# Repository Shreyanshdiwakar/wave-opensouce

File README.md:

# Wave - Open Source Analog Keyboard

I use the two prototypes shown above as my daily drivers for both coding and gaming. They work well, and the current state of the web configurator is sufficient for seamlessly switching between coding and gaming modes. The current layout of my prototypes is Mac ISO azerty (FR).

## Videos

### 3D Printing Process

▶️ [Watch 3D Printing Process Video](assets/3dprinter.mp4)

### Keyboard Demonstration
▶️ [Watch Keyboard Demonstration Video](assets/keyboard.mp4)

Other videos:
- ▶️ [PCB overview](assets/pcb.mp4)
- ▶️ [Rev 2 demonstration](assets/rev%202.mp4)

## Features

- **Analog Input:** Each key detects varying levels of pressure thanks to Hall Effect technology, allowing for a more responsive and sensitive typing experience.
- **Rapid Trigger Support:** Enables keys to actuate without fully releasing, allowing for faster response times during intense usage (e.g., gaming or rapid typing).
- **Continuous Rapid Trigger:** For keys that require repeated pressing (e.g., in gaming), this feature allows automatic repeated key input with a single press.
- **Tap and Hold Functionality:** Each key can be assigned two functions. A tap function for quick presses and a hold function for longer presses. This is ideal for combining shortcuts or creating multi-functional keys, such as assigning the right Shift key to act as an arrow up when tapped.
- **Web-Based Configurator:** Allows customization of key sensitivity and rapid trigger settings, with future updates planned to enable key mapping and expanded functionality. (see [screenshot](assets/web-configurator-screenshot.png))

## Todos

This is still a work in progress, the first revision is working flawlessly but it is not that configurable yet. Here is some of the things I'm working on right now

- [x] PCB Rev 2.0
- [ ] Explore other MCUs
  - [ ] esp32-s3 (in progress)
  - [ ] nRF52840
  - [ ] RP2354 ?
- [ ] Add Bluetooth
- [ ] Configure layout and key mapping from the web interface
- [ ] Improve performances

## Links

- [keyboard layout](http://www.keyboard-layout-editor.com/#/gists/9dc992fd631d9f29cc5bdf738b10b4e4)

## Misc

### References

- ~~[RP2040 Datasheet](https://datasheets.raspberrypi.com/rp2040/rp2040-datasheet.pdf)~~
- ~~[RP2040 Hardware Design](https://datasheets.raspberrypi.com/rp2040/hardware-design-with-rp2040.pdf)~~
- ~~[kb2040 doc](https://learn.adafruit.com/adafruit-kb2040/downloads)~~
- ~~[RPi Pico Debugger Shoe](https://github.com/ShawnHymel/rpi-pico-debugger-shoe)~~
- [Dilemma keyboard](https://github.com/Bastardkb/Dilemma)
- [0xB2 - splinky](https://github.com/plut0nium/0xB2)
- [Sub Reddit](https://www.reddit.com/r/PrintedCircuitBoard/search/?q=rp2040&restrict_sr=1&sr_nsfw=&include_over_18=1)
- [layout/design ref](https://geekhack.org/index.php?topic=103671.0)
- [cirque trackpad](https://www.cirque.com/glidepoint-circle-trackpads)
- [MagLev_Switch_MX](https://github.com/famichu/MagLev_Switch_MX)
- [Anatomy of a keyboard](https://matt3o.com/anatomy-of-a-keyboard/)
- [Switches/Stabs Kicad footprints from ebastler/marbastlib](https://github.com/ebastler/marbastlib)
- [Reddit Post about someone building a lekker switch based keyboard](https://www.reddit.com/r/PrintedCircuitBoard/comments/152kt63/review_request_analog_hall_effect_75_iso_keyboard/)
- [Riskable projects](https://github.com/riskable)
- [Fluxpad with lekker switches](https://github.com/sssata/fluxpad)
- [STM32F411CEU6 documentation](https://www.st.com/en/microcontrollers-microprocessors/stm32f411ce.html#documentation)
- [Wooting 60HE pcb](https://github.com/heiso/macrolev/tree/main/ref/Wooting-60HE)
- [Connecting to uncommon HID devices](https://developer.chrome.com/articles/hid)
- [HID Descriptor parser](https://eleccelerator.com/usbdescreqparser/)
- [peppapighs HE8 keyboard](https://github.com/peppapighs/HE8)
- [peppapighs libhmk library](https://github.com/peppapighs/libhmk)
- [nuphy configurator demo](https://drive.nuphy.io/?isDemoMode=true)
- [geonworks configurator demo](https://venom.how/)
- [wooting configurator demo](https://wootility.io/)

### Tooling

- [QMK keyboard test](https://config.qmk.fm/#/test)
- [Keyboard ghosting interactive demonstration](https://www.microsoft.com/applied-sciences/projects/anti-ghosting-demo)
- [Kicad lib marbastlib](https://github.com/ebastler/marbastlib)
- [Debug HardFault](https://interrupt.memfault.com/blog/cortex-m-hardfault-debug)
- [ai03 Plate Generator](https://kbplate.ai03.com/)
- [JLC2KiCad_lib](https://github.com/TousstNicolas/JLC2KiCad_lib)

Add footprints and symbols from jlcpcb with this cmd

```bash
JLC2KiCadLib <...LCSC refs> -dir JLCPCB -symbol_lib JLCPCB
```

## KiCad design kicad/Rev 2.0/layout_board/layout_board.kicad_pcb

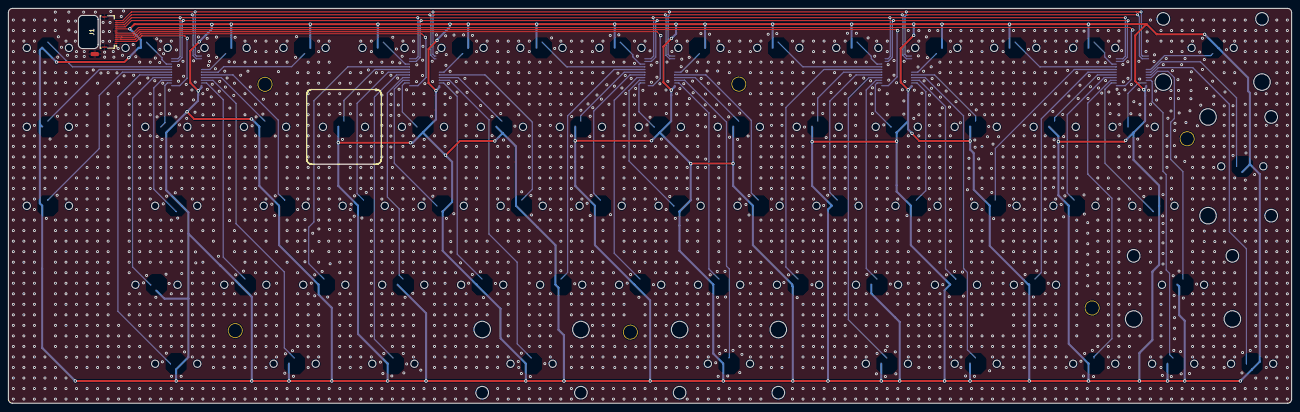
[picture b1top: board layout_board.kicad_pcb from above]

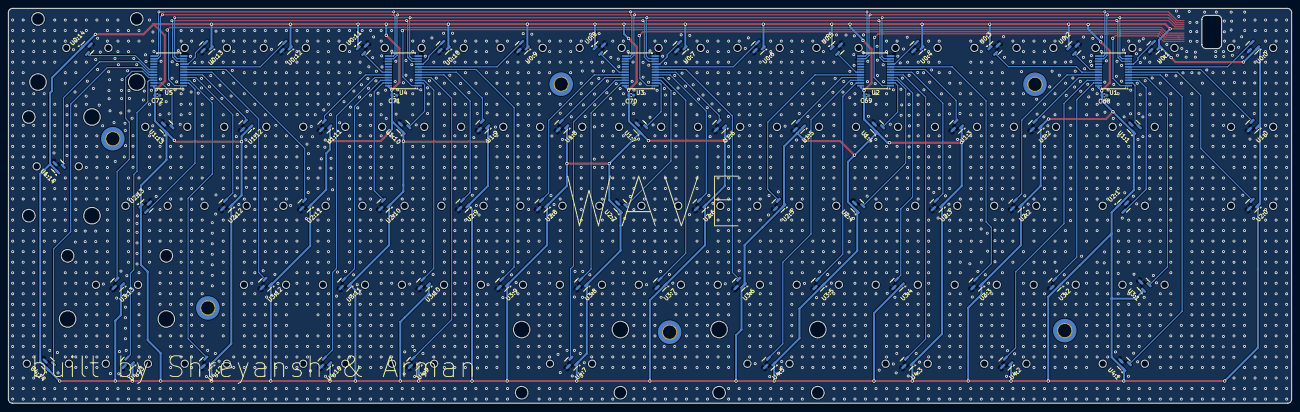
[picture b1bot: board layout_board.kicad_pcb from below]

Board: 2 copper layers, 309.6 x 95.2 mm, 78 parts (77 on the bottom side), 78 nets.

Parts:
C68, C69, C70, C71, C72: 100n; C_0402_1005Metric_Pad0.74x0.62mm_HandSolder
J1: HC-FPC-05-10-12RLTAG; FPC-SMD_12P-P0.50_HCTL_HC-FPC-05-10-12RLTAG
U0:0, U0:1, U0:2, U0:3, U0:4, U0:5, U0:6, U0:7, U0:8, U0:9, U0:10, U0:11, U0:12, U0:13, U0:14, U1:0, U1:1, U1:2, U1:3, U1:4, U1:5, U1:6, U1:7, U1:8, U1:9, U1:10, U1:11, U1:12, U1:13, U1:14, U2:0, U2:1, U2:2, U2:3, U2:4, U2:5, U2:6, U2:7, U2:8, U2:9, U2:10, U2:11, U2:12, U2:13, U3:1, U3:2, U3:3, U3:4, U3:5, U3:6, U3:7, U3:8, U3:9, U3:10, U3:11, U3:12, U3:13, U4:1, U4:2, U4:3, U4:5, U4:7, U4:9, U4:10, U4:12, U4:13, U4:14: GH39FKSW; SOT-23
U1, U2, U3, U4, U5: CD4067BPWR; SSOP-24_5.3x8.2mm_P0.65mm

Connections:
+3.3VA: C68.1, C69.1, C70.1, C71.1, C72.1, J1.8, U0:0.1 (VDD), U0:1.1 (VDD), U0:2.1 (VDD), U0:3.1 (VDD), U0:4.1 (VDD), U0:5.1 (VDD), U0:6.1 (VDD), U0:7.1 (VDD), U0:8.1 (VDD), U0:9.1 (VDD), U0:10.1 (VDD), U0:11.1 (VDD), U0:12.1 (VDD), U0:13.1 (VDD), U0:14.1 (VDD), U1.24 (VDD), U1:0.1 (VDD), U1:1.1 (VDD), U1:2.1 (VDD), U1:3.1 (VDD), U1:4.1 (VDD), U1:5.1 (VDD), U1:6.1 (VDD), U1:7.1 (VDD), U1:8.1 (VDD), U1:9.1 (VDD), U1:10.1 (VDD), U1:11.1 (VDD), U1:12.1 (VDD), U1:13.1 (VDD), U1:14.1 (VDD), U2.24 (VDD), U2:0.1 (VDD), U2:1.1 (VDD), U2:2.1 (VDD), U2:3.1 (VDD), U2:4.1 (VDD), U2:5.1 (VDD), U2:6.1 (VDD), U2:7.1 (VDD), U2:8.1 (VDD), U2:9.1 (VDD), U2:10.1 (VDD), U2:11.1 (VDD), U2:12.1 (VDD), U2:13.1 (VDD), U3.24 (VDD), U3:1.1 (VDD), U3:2.1 (VDD), U3:3.1 (VDD), U3:4.1 (VDD), U3:5.1 (VDD), U3:6.1 (VDD), U3:7.1 (VDD), U3:8.1 (VDD), U3:9.1 (VDD), U3:10.1 (VDD), U3:11.1 (VDD), U3:12.1 (VDD), U3:13.1 (VDD), U4.24 (VDD), U4:1.1 (VDD), U4:2.1 (VDD), U4:3.1 (VDD), U4:5.1 (VDD), U4:7.1 (VDD), U4:9.1 (VDD), U4:10.1 (VDD), U4:12.1 (VDD), U4:13.1 (VDD), U4:14.1 (VDD), U5.24 (VDD)
/ADC0: J1.2, U1.1 (COMMONOUT/IN)
/ADC1: J1.3, U2.1 (COMMONOUT/IN)
/ADC2: J1.4, U3.1 (COMMONOUT/IN)
/ADC3: J1.5, U4.1 (COMMONOUT/IN)
/ADC4: J1.6, U5.1 (COMMONOUT/IN)
/AMUX0:0: U0:1.2 (VOUT), U1.9 (0)
/AMUX0:1: U0:0.2 (VOUT), U1.8 (1)
/AMUX0:2: U1.7 (2), U1:0.2 (VOUT)
/AMUX0:3: U1.6 (3), U2:0.2 (VOUT)
/AMUX0:4: U1.5 (4), U4:1.2 (VOUT)
/AMUX0:5: U1.4 (5), U3:1.2 (VOUT)
/AMUX0:6: U1.3 (6), U2:1.2 (VOUT)
/AMUX0:7: U1.2 (7), U1:1.2 (VOUT)
/AMUX0:8: U1.23 (8), U3:2.2 (VOUT)
/AMUX0:9: U1.22 (9), U4:2.2 (VOUT)
/AMUX0:10: U1.21 (10), U1:2.2 (VOUT)
/AMUX0:11: U1.20 (11), U2:2.2 (VOUT)
/AMUX0:12: U0:3.2 (VOUT), U1.19 (12)
/AMUX0:13: U0:2.2 (VOUT), U1.18 (13)
/AMUX1:0: U0:4.2 (VOUT), U2.9 (0)
/AMUX1:1: U2.8 (1), U3:3.2 (VOUT)
/AMUX1:2: U1:3.2 (VOUT), U2.7 (2)
/AMUX1:3: U2.6 (3), U2:3.2 (VOUT)
/AMUX1:4: U2.5 (4), U4:3.2 (VOUT)
/AMUX1:5: U2.4 (5), U3:4.2 (VOUT)
/AMUX1:6: U2.3 (6), U2:4.2 (VOUT)
/AMUX1:7: U1:4.2 (VOUT), U2.2 (7)
/AMUX1:8: U2.23 (8), U3:5.2 (VOUT)
/AMUX1:9: U2.22 (9), U4:5.2 (VOUT)
/AMUX1:10: U1:5.2 (VOUT), U2.21 (10)
/AMUX1:11: U2.20 (11), U2:5.2 (VOUT)
/AMUX1:12: U0:5.2 (VOUT), U2.19 (12)
/AMUX2:0: U0:7.2 (VOUT), U3.9 (0)
/AMUX2:1: U0:6.2 (VOUT), U3.8 (1)
/AMUX2:2: U3.7 (2), U3:6.2 (VOUT)
/AMUX2:3: U1:6.2 (VOUT), U3.6 (3)
/AMUX2:4: U2:6.2 (VOUT), U3.5 (4)
/AMUX2:5: U3.4 (5), U3:7.2 (VOUT)
/AMUX2:6: U2:7.2 (VOUT), U3.3 (6)
/AMUX2:7: U1:7.2 (VOUT), U3.2 (7)
/AMUX2:8: U3.23 (8), U3:8.2 (VOUT)
/AMUX2:9: U3.22 (9), U4:7.2 (VOUT)
/AMUX2:10: U1:8.2 (VOUT), U3.21 (10)
/AMUX2:11: U2:8.2 (VOUT), U3.20 (11)
/AMUX2:12: U0:8.2 (VOUT), U3.19 (12)
/AMUX3:0: U0:10.2 (VOUT), U4.9 (0)
/AMUX3:1: U0:9.2 (VOUT), U4.8 (1)
/AMUX3:2: U3:9.2 (VOUT), U4.7 (2)
/AMUX3:3: U1:9.2 (VOUT), U4.6 (3)
/AMUX3:4: U2:9.2 (VOUT), U4.5 (4)
/AMUX3:5: U4.4 (5), U4:9.2 (VOUT)
/AMUX3:6: U3:10.2 (VOUT), U4.3 (6)
/AMUX3:7: U1:10.2 (VOUT), U4.2 (7)
/AMUX3:8: U2:10.2 (VOUT), U4.23 (8)
/AMUX3:9: U3:11.2 (VOUT), U4.22 (9)
/AMUX3:10: U4.21 (10), U4:10.2 (VOUT)
/AMUX3:11: U1:11.2 (VOUT), U4.20 (11)
/AMUX3:12: U0:11.2 (VOUT), U4.19 (12)
/AMUX4:0: U0:13.2 (VOUT), U5.9 (0)
/AMUX4:1: U0:12.2 (VOUT), U5.8 (1)
/AMUX4:2: U2:11.2 (VOUT), U5.7 (2)
/AMUX4:3: U3:12.2 (VOUT), U5.6 (3)
/AMUX4:4: U1:12.2 (VOUT), U5.5 (4)
/AMUX4:5: U2:12.2 (VOUT), U5.4 (5)
/AMUX4:6: U4:12.2 (VOUT), U5.3 (6)
/AMUX4:7: U2:13.2 (VOUT), U5.2 (7)
/AMUX4:8: U1:13.2 (VOUT), U5.23 (8)
/AMUX4:9: U4:13.2 (VOUT), U5.22 (9)
/AMUX4:10: U3:13.2 (VOUT), U5.21 (10)
/AMUX4:11: U4:14.2 (VOUT), U5.20 (11)
/AMUX4:12: U1:14.2 (VOUT), U5.19 (12)
/AMUX4:13: U0:14.2 (VOUT), U5.18 (13)
/SELECT0: J1.9, U1.10 (A), U2.10 (A), U3.10 (A), U4.10 (A), U5.10 (A)
/SELECT1: J1.10, U1.11 (B), U2.11 (B), U3.11 (B), U4.11 (B), U5.11 (B)
/SELECT2: J1.11, U1.14 (C), U2.14 (C), U3.14 (C), U4.14 (C), U5.14 (C)
/SELECT3: J1.12, U1.13 (D), U2.13 (D), U3.13 (D), U4.13 (D), U5.13 (D)
GND: C68.2, C69.2, C70.2, C71.2, C72.2, J1.1, J1.7, J1.13, J1.14, U0:0.3 (GND), U0:1.3 (GND), U0:2.3 (GND), U0:3.3 (GND), U0:4.3 (GND), U0:5.3 (GND), U0:6.3 (GND), U0:7.3 (GND), U0:8.3 (GND), U0:9.3 (GND), U0:10.3 (GND), U0:11.3 (GND), U0:12.3 (GND), U0:13.3 (GND), U0:14.3 (GND), U1.12 (VSS), U1.15 (INHIBT), U1:0.3 (GND), U1:1.3 (GND), U1:2.3 (GND), U1:3.3 (GND), U1:4.3 (GND), U1:5.3 (GND), U1:6.3 (GND), U1:7.3 (GND), U1:8.3 (GND), U1:9.3 (GND), U1:10.3 (GND), U1:11.3 (GND), U1:12.3 (GND), U1:13.3 (GND), U1:14.3 (GND), U2.12 (VSS), U2.15 (INHIBT), U2:0.3 (GND), U2:1.3 (GND), U2:2.3 (GND), U2:3.3 (GND), U2:4.3 (GND), U2:5.3 (GND), U2:6.3 (GND), U2:7.3 (GND), U2:8.3 (GND), U2:9.3 (GND), U2:10.3 (GND), U2:11.3 (GND), U2:12.3 (GND), U2:13.3 (GND), U3.12 (VSS), U3.15 (INHIBT), U3:1.3 (GND), U3:2.3 (GND), U3:3.3 (GND), U3:4.3 (GND), U3:5.3 (GND), U3:6.3 (GND), U3:7.3 (GND), U3:8.3 (GND), U3:9.3 (GND), U3:10.3 (GND), U3:11.3 (GND), U3:12.3 (GND), U3:13.3 (GND), U4.12 (VSS), U4.15 (INHIBT), U4:1.3 (GND), U4:2.3 (GND), U4:3.3 (GND), U4:5.3 (GND), U4:7.3 (GND), U4:9.3 (GND), U4:10.3 (GND), U4:12.3 (GND), U4:13.3 (GND), U4:14.3 (GND), U5.12 (VSS), U5.15 (INHIBT)
